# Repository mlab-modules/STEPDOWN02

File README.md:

# STEPDOWN02 - 1MHz switching down converter

This repository contains the design files, documentation, and usage instructions for the TPS54332 MLAB module. The TPS54332 is a high-efficiency synchronous buck converter capable of delivering up to 3 A of continuous output current. This development module is designed to integrate the TPS54332 into MLAB projects with ease.

## Features

- **Input Voltage Range**: 3.5 V to 28 V
- **Output Voltage Range**: 0.8 V to 23 V
- **Output Current**: Up to 3 A
- **Efficiency**: Up to 95%
- **Switching Frequency**: Adjustable up to 2 MHz
- **Integrated High-Side and Low-Side MOSFETs**
- **Cycle-by-Cycle Current Limit, Frequency Fold Back and Thermal Shutdown Protection**

## Getting Started

### Prerequisites

To use this development module, you will need:

- A DC power supply (3.5 V to 28 V)
- Load device (up to 3 A)
- Multimeter or oscilloscope for measurements
- Soldering equipment (if customization of output voltage is needed)

### Installation

1. **Connect the Power Supply**: Connect the positive terminal of your DC power supply to the VIN pin and the negative terminal to the GND pin of the module.
2. **Connect the Load**: Connect your load device between the VOUT pin and GND pin of the module.

### Usage

1. **Adjust Output Voltage**: The output voltage can be adjusted by selecting appropriate values for the feedback resistors (R1 and R2). Refer to the datasheet for the resistor calculation formula.
2. **Monitoring**: Use a multimeter or oscilloscope to monitor the output voltage and current.
3. **Optimization**: Fine-tune the switching frequency and compensation network as required for your application.

## Documentation

- **Datasheet**: [TPS54332 Datasheet](https://www.ti.com/product/TPS54332)

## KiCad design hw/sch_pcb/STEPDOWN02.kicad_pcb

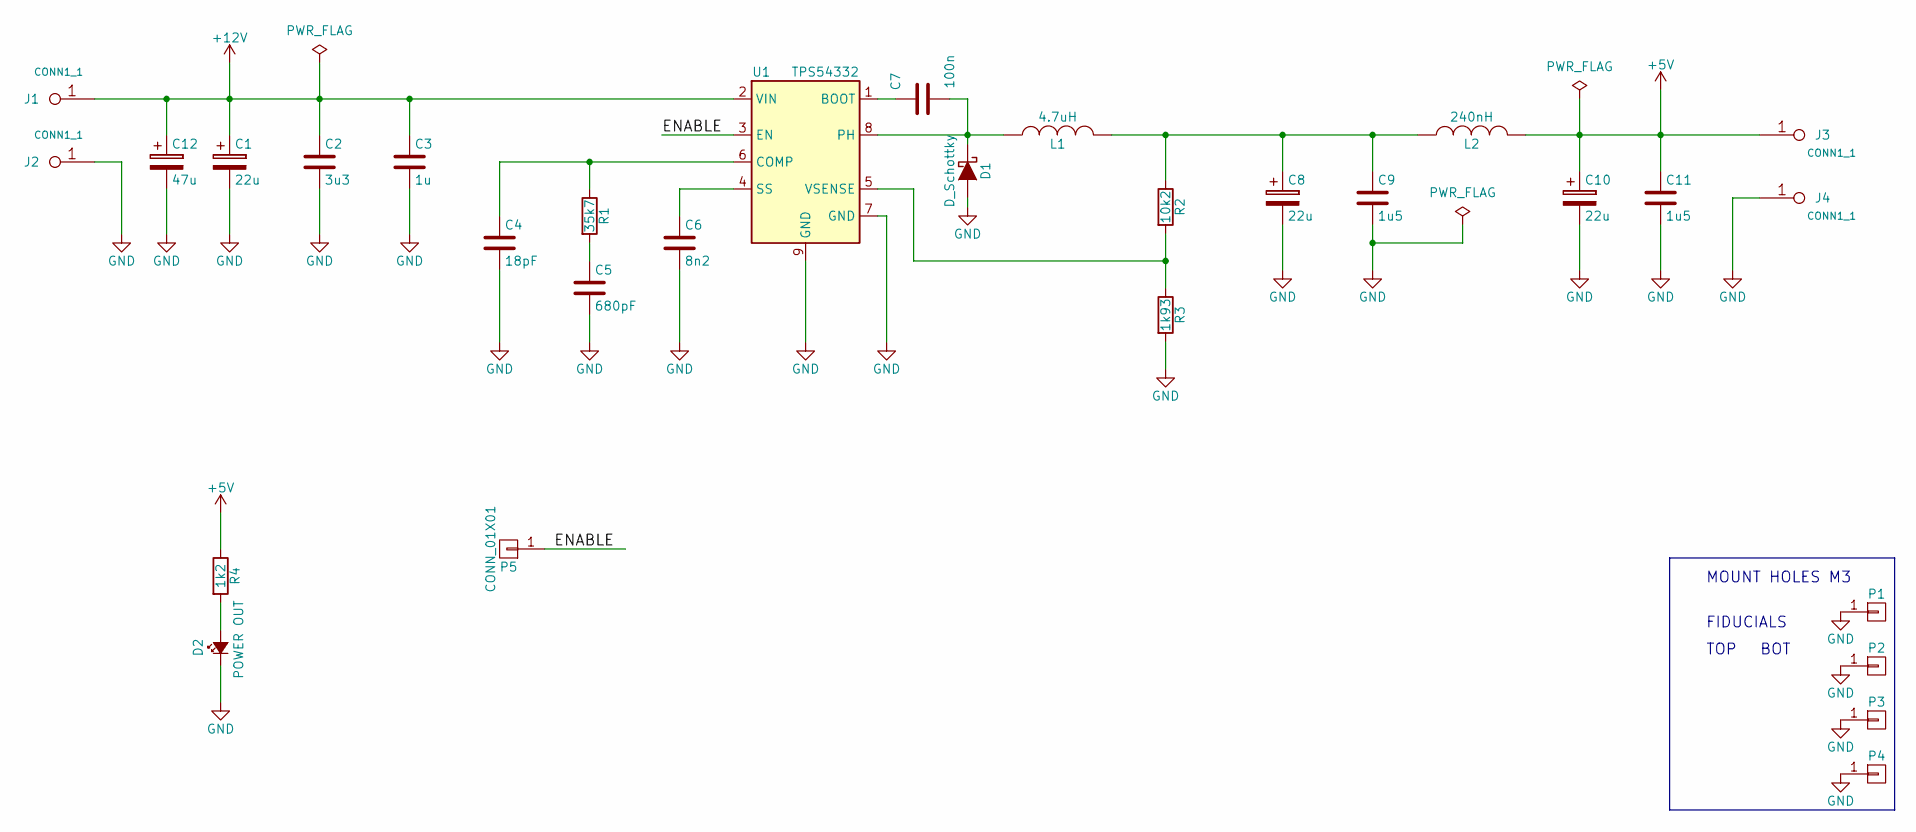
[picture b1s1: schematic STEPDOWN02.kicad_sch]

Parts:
C1: 22u; TantalC_SizeD_EIA-7343_Reflow
C2: 3u3; C_0805
C3: 1u; C_0805
C4: 18pF; C_0805
C5: 680pF; C_0805
C6: 8n2; C_0805
C7: 100n; C_0805
C8: 22u; TantalC_SizeC_EIA-6032_Reflow
C9, C11: 1u5; C_1206
C10: 22u; TantalC_SizeB_EIA-3528_Reflow
C12: 47u; C_Radial_D6.3_L11.2_P2.5
D1: D_Schottky; DO-214AB
D2: POWER OUT; LED_0805
J1, J2, J3, J4: CONN1_1; WAGO256
L1: 4.7uH; Inductor_XAL4030-472MEB
L2: 240nH; R_0805
P1, P2, P3, P4: _NC; MountingHole_3.2mm_M3_DIN965_Pad
P5: CONN_01X01; Pin_Header_Straight_1x01
R1: 35k7; R_0805
R2: 10k2; R_0805
R3: 1k93; R_0805
R4: 1k2; R_0805
U1: TPS54332; 8-PowerSOIC_Pitch1.27mm

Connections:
+5V: C10.1, C11.1, J3.1, L2.2, R4.1
+12V: C1.1, C2.1, C3.1, C12.1, J1.1, U1.2 (VIN)
/ENABLE: P5.1, U1.3 (EN)
GND: C1.2, C2.2, C3.2, C4.2, C5.2, C6.2, C8.2, C9.2, C10.2, C11.2, C12.2, D1.2 (A), D2.1 (K), J2.1, J4.1, P1.1, P2.1, P3.1, P4.1, R3.2, U1.7 (GND), U1.9 (GND)
unnamed: C4.1, R1.1, U1.6 (COMP)
unnamed: C5.1, R1.2
unnamed: C6.1, U1.4 (SS)
unnamed: C7.1, D1.1 (K), L1.1, U1.8 (PH)
unnamed: C7.2, U1.1 (BOOT)
unnamed: C8.1, C9.1, L1.2, L2.1, R2.1
unnamed: D2.2 (A), R4.2
unnamed: R2.2, R3.1, U1.5 (VSENSE)

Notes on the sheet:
BOT
FIDUCIALS
TOP
MOUNT HOLES M3

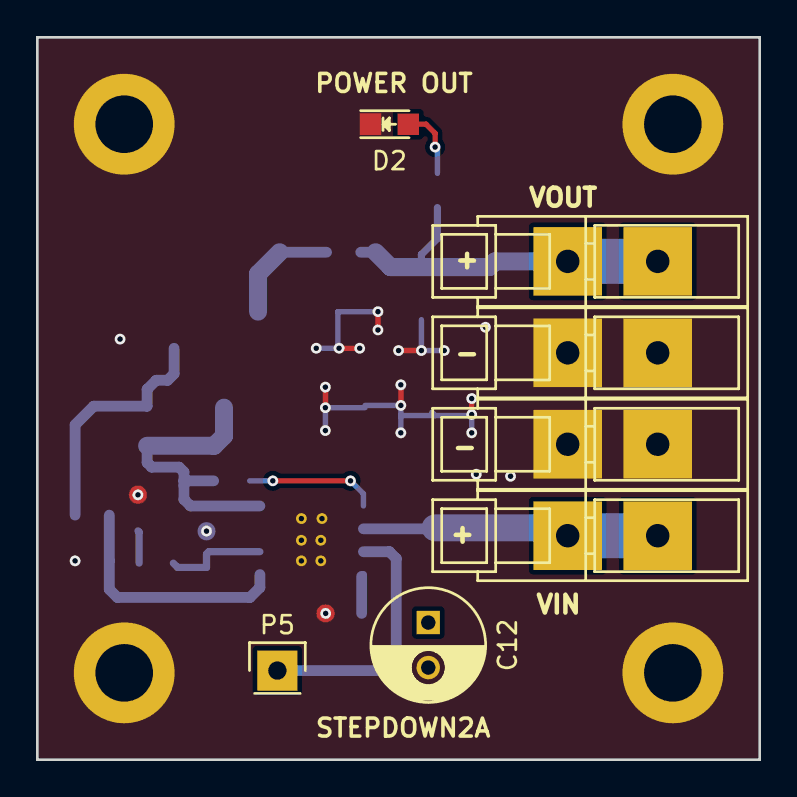
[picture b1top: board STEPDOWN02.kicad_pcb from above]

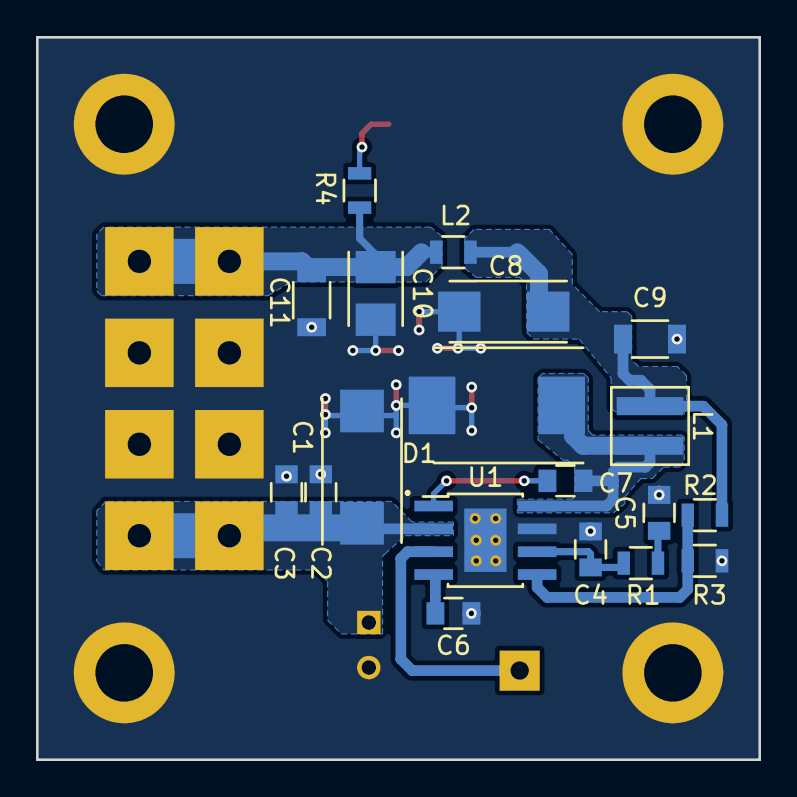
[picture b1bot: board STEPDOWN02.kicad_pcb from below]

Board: 2 copper layers, 40.1 x 40.1 mm, 30 parts (19 on the bottom side), 12 nets.

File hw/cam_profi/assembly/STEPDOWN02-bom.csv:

Component,Description,Part,References,Value,Footprint,Quantity Per PCB,Datasheet
1,,C,C4,18pF,C_0805,1,
2,,C,C5,680pF,C_0805,1,
3,,C,C6,8n2,C_0805,1,
4,,C,C7,100n,C_0805,1,
5,,C,C3,1u,C_0805,1,
6,,C,C9C11,1u5,C_1206,2,
7,,C,C2,3u3,C_0805,1,
8,,CP,C1,22u,TantalC_SizeD_EIA-7343_Reflow,1,
9,,CP,C10,22u,TantalC_SizeB_EIA-3528_Reflow,1,
10,,CP,C8,22u,TantalC_SizeC_EIA-6032_Reflow,1,
11,,CP,C12,47u,C_Radial_D6.3_L11.2_P2.5,1,
12,,D_Schottky,D1,D_Schottky,DO-214AB,1,
13,,Led_Small,D2,POWER OUT,LED_0805,1,
14,,CONN1_1,J1J2J3J4,CONN1_1,WAGO256,4,
15,,INDUCTOR,L2,240nH,R_0805,1,
16,,INDUCTOR,L1,4.7uH,Inductor_XAL4030-472MEB,1,
17,,CONN_01X01,P5,CONN_01X01,Pin_Header_Straight_1x01,1,
18,,R,R4,1k2,R_0805,1,
19,,R,R3,1k93,R_0805,1,
20,,R,R2,10k2,R_0805,1,
21,,R,R1,35k7,R_0805,1,
22,,TPS54332,U1,TPS54332,8-PowerSOIC_Pitch1.27mm,1,

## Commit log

2020-12-05 Initial commit.
2022-04-06 automated commit; add github actions
2023-05-25 Update metadata files
2023-05-28 Update workflow files
2023-09-16 Update status
2023-09-17 Convert project to KiCAD7 format.
2023-09-17 Update actions products
2023-09-17 Update metadata.yaml
    select title image.
2024-07-03 Update module readme.
2024-07-03 update actions.
